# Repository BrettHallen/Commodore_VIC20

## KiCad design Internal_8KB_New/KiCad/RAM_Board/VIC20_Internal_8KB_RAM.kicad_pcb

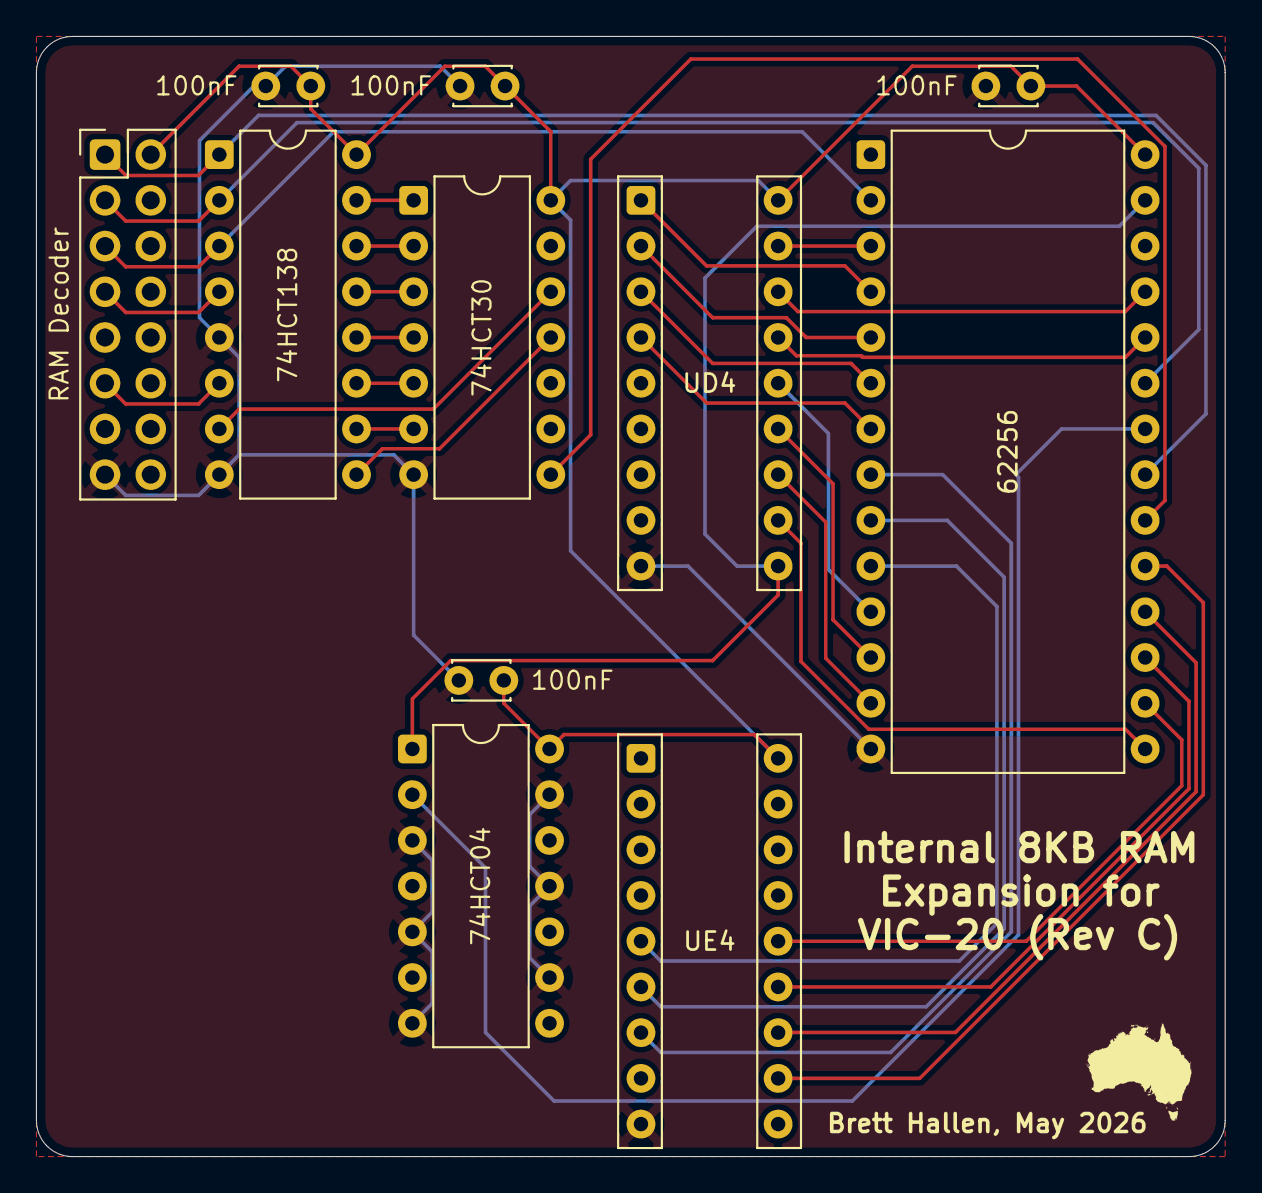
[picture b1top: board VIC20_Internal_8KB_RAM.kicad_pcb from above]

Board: 2 copper layers, 66.0 x 62.2 mm, 11 parts (0 on the bottom side), 36 nets.

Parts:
C1, C2, C3, C4: 100nF; C_Disc_D3.0mm_W2.0mm_P2.50mm
J1: RAM Decoder; PinHeader_2x08_P2.54mm_Vertical
J2: UD4; DIP-18_W7.62mm
J3: UE4; DIP-18_W7.62mm
U1: 74HCT04; DIP-14_W7.62mm
U2: 74HCT138; DIP-16_W7.62mm
U3: 62256; DIP-28_W15.24mm
U4: 74HCT30; DIP-14_W7.62mm

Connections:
+5V: C1.1, C2.1, C3.1, C4.1, J1.16, J2.18, J3.18, U1.14 (VCC), U2.16 (VCC), U3.28 (VCC), U4.14 (VCC)
/BD0: J2.14, U3.11 (Q0)
/BD1: J2.13, U3.12 (Q1)
/BD2: J2.12, U3.13 (Q2)
/BD3: J2.11, U3.15 (Q3)
/BD4: J3.14, U3.16 (Q4)
/BD5: J3.13, U3.17 (Q5)
/BD6: J3.12, U3.18 (Q6)
/BD7: J3.11, U3.19 (Q7)
/VA0: J3.5, U3.10 (A0)
/VA1: J3.6, U3.9 (A1)
/VA2: J3.7, U3.8 (A2)
/VA3: J2.4, U3.7 (A3)
/VA4: J2.3, U3.6 (A4)
/VA5: J2.2, U3.5 (A5)
/VA6: J2.1, U3.4 (A6)
/VA7: J2.17, U3.3 (A7)
/VA8: J2.16, U3.25 (A8)
/VA9: J2.15, U3.24 (A9)
/VA10: J1.1, U2.1 (A0), U3.21 (A10)
/VA11: J1.2, U2.2 (A1), U3.23 (A11)
/VA12: J1.3, U2.3 (A2), U3.2 (A12)
/VA13/G1: J1.6, U2.6 (E2)
/VR/~W: J2.10, U1.1, U3.27 (~WE)
/~BLK0/~G2A: J1.4, U2.4 (~E0)
/~OE: U1.2, U3.22 (~OE)
/~RAM0: U2.15 (~Y0), U4.1
/~RAM1: U2.14 (~Y1), U4.2
/~RAM2: U2.13 (~Y2), U4.3
/~RAM3: U2.12 (~Y3), U4.4
/~RAM4: U2.11 (~Y4), U4.5
/~RAM5: U2.10 (~Y5), U4.6
/~RAM6: U2.9 (~Y6), U4.11
/~RAM7: U2.7 (~Y7), U4.12
/~RAM_CS: U3.20 (~CS), U4.8
GND: C1.2, C2.2, C3.2, C4.2, J1.8, J2.9, J3.9, U1.3, U1.5, U1.7 (GND), U1.9, U1.11, U1.13, U2.5 (~E1), U2.8 (GND), U3.14 (GND), U4.7 (GND)

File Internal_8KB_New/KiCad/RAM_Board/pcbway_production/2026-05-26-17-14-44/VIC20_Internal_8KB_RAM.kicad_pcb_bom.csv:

Designator,Quantity,Value,Footprint,Package,MPN,DNP,Mount_Type,Description
"C1, C2, C3, C4",4,100nF,C_Disc_D3.0mm_W2.0mm_P2.50mm,,,,tht,Unpolarized capacitor
J1,1,RAM Decoder,PinHeader_2x08_P2.54mm_Vertical,,,,tht,"Generic connector, double row, 02x08, counter clockwise pin numbering scheme (similar to DIP package numbering), script generated (kicad-library-utils/schlib/autogen/connector/)"
J2,1,UD4,DIP-18_W7.62mm,,,,tht,"Generic connector, double row, 02x09, counter clockwise pin numbering scheme (similar to DIP package numbering), script generated (kicad-library-utils/schlib/autogen/connector/)"
J3,1,UE4,DIP-18_W7.62mm,,,,tht,"Generic connector, double row, 02x09, counter clockwise pin numbering scheme (similar to DIP package numbering), script generated (kicad-library-utils/schlib/autogen/connector/)"
U1,1,74HCT04,DIP-14_W7.62mm,,,,tht,Hex Inverter
U2,1,74HCT138,DIP-16_W7.62mm,,,,tht,"3-to-8 line decoder/multiplexer inverting, DIP-16/SOIC-16/SSOP-16"
U3,1,62256,DIP-28_W15.24mm,,,,tht,"32,768-word × 8-bit High Speed CMOS Static RAM, 70ns, DIP-28"
U4,1,74HCT30,DIP-14_W7.62mm,,,,tht,8-input NAND

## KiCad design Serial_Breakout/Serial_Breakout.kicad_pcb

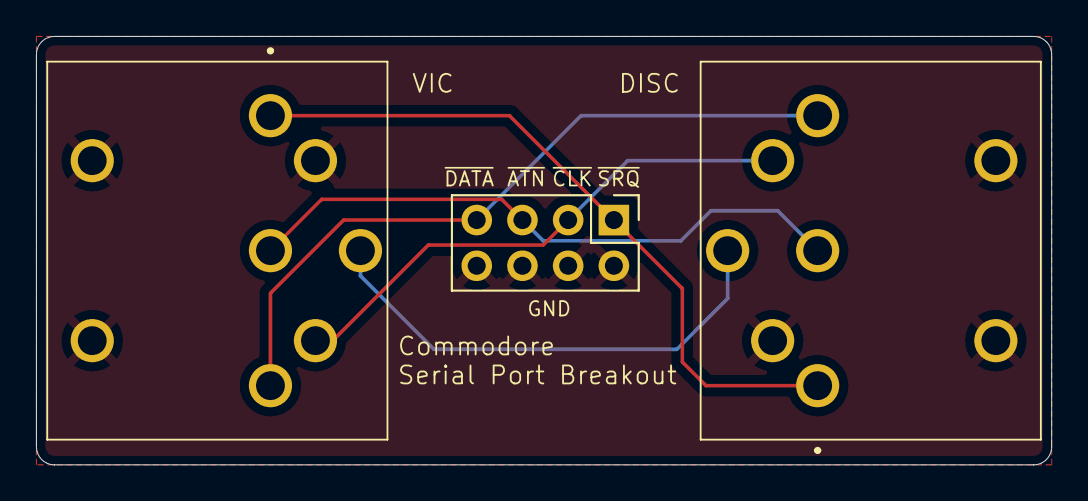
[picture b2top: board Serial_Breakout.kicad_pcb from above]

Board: 2 copper layers, 56.4 x 23.8 mm, 3 parts (0 on the bottom side), 6 nets.

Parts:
J1: VIC Serial In; 6710601
J2: Disc Serial Out; 6710601
J3: Breakout; PinHeader_2x04_P2.54mm_Vertical

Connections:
/GND: J1.2 (GND), J1.MH1, J1.MH2, J2.2 (GND), J2.MH1, J2.MH2, J3.2, J3.4, J3.6, J3.8
/~ATN: J1.3 (~ATN), J2.3 (~ATN), J3.5
/~CLK: J1.4 (~CLK), J2.4 (~CLK), J3.3
/~DATA: J1.5 (~DATA), J2.5 (~DATA), J3.7
/~RESET: J1.6 (~RESET), J2.6 (~RESET)
/~SRQIN: J1.1 (~SRQIN), J2.1 (~SQRIN), J3.1

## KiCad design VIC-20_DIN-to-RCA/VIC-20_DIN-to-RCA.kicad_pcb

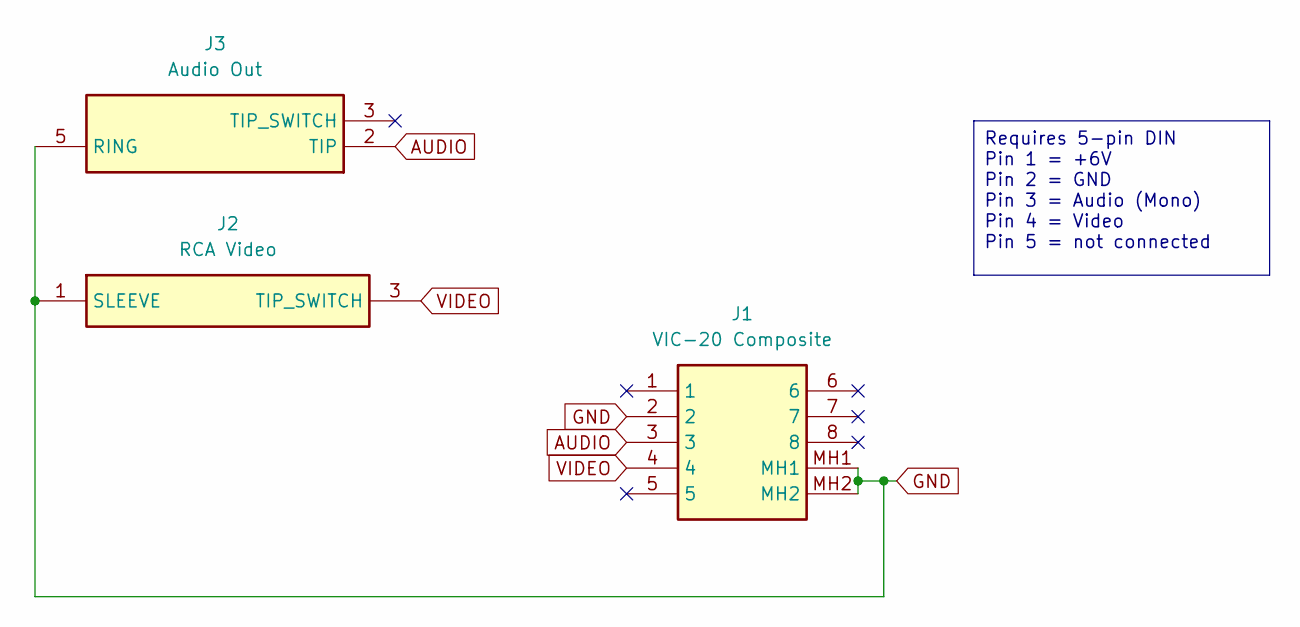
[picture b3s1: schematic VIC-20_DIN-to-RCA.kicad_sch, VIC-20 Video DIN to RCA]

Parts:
J1: VIC-20 Composite; 6710801; Manufacturer_Part_Number 671-0801
J2: RCA Video; FC68371; Manufacturer_Part_Number FC68371
J3: Audio Out; SJ3350820BTR; Mouser Part Number 179-SJ3-350820B-TR

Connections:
AUDIO: J1.3, J3.2 (TIP)
GND: J1.2, J1.MH1, J1.MH2, J2.1 (SLEEVE), J3.5 (RING)
VIDEO: J1.4, J2.3 (TIP_SWITCH)

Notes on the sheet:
Requires 5-pin DIN Pin 1 = +6V Pin 2 = GND Pin 3 = Audio (Mono) Pin 4 = Video Pin 5 = not connected

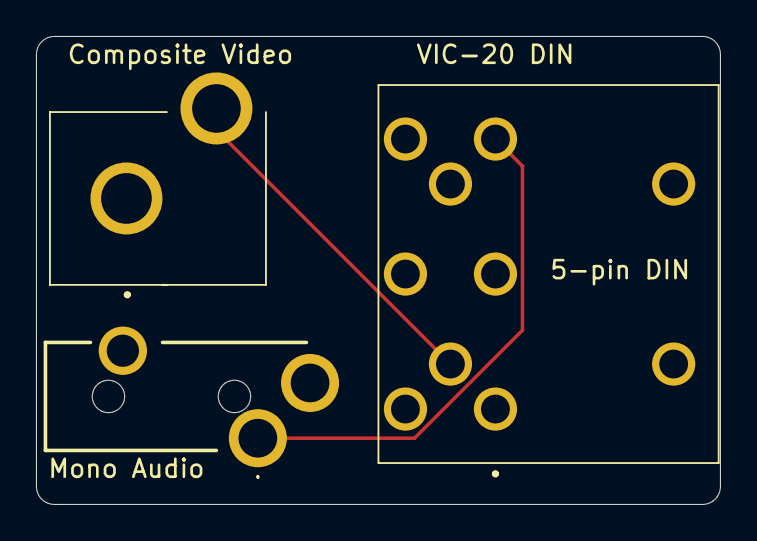
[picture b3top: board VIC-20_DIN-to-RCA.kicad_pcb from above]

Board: 2 copper layers, 38.0 x 26.0 mm, 3 parts (0 on the bottom side), 3 nets.

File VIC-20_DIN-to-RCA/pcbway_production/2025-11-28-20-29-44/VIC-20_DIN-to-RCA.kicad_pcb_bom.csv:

Designator,Quantity,Value,Footprint,Package,MPN,DNP,Mount_Type,Description,Height,Manufacturer_Name,Mouser Part Number,Mouser Price/Stock
J1,1,VIC-20 Composite,6710801,,671-0801,,tht,"Deltron 8 Pole Right Angle Din Socket Socket, 2A, 100 V ac, Lockable",19.5,DELTRON COMPONENTS,,
J2,1,RCA Video,FC68371,,FC68371,,tht,Socket; RCA; female; angled 90; THT; nickel plated; Marker: black,14,CLIFF ELECTRONIC COMPONENTS,,
J3,1,Audio Out,SJ3350820BTR,,SJ3-350820B-TR,,tht,"3.5 mm Stereo Jack, Through Hole, 2 Conductors, 1 Internal Switches,  Tape & Reel Packaging",5.3,Same Sky,179-SJ3-350820B-TR,https://www.mouser.co.uk/ProductDetail/Same-Sky/SJ3-350820B-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
